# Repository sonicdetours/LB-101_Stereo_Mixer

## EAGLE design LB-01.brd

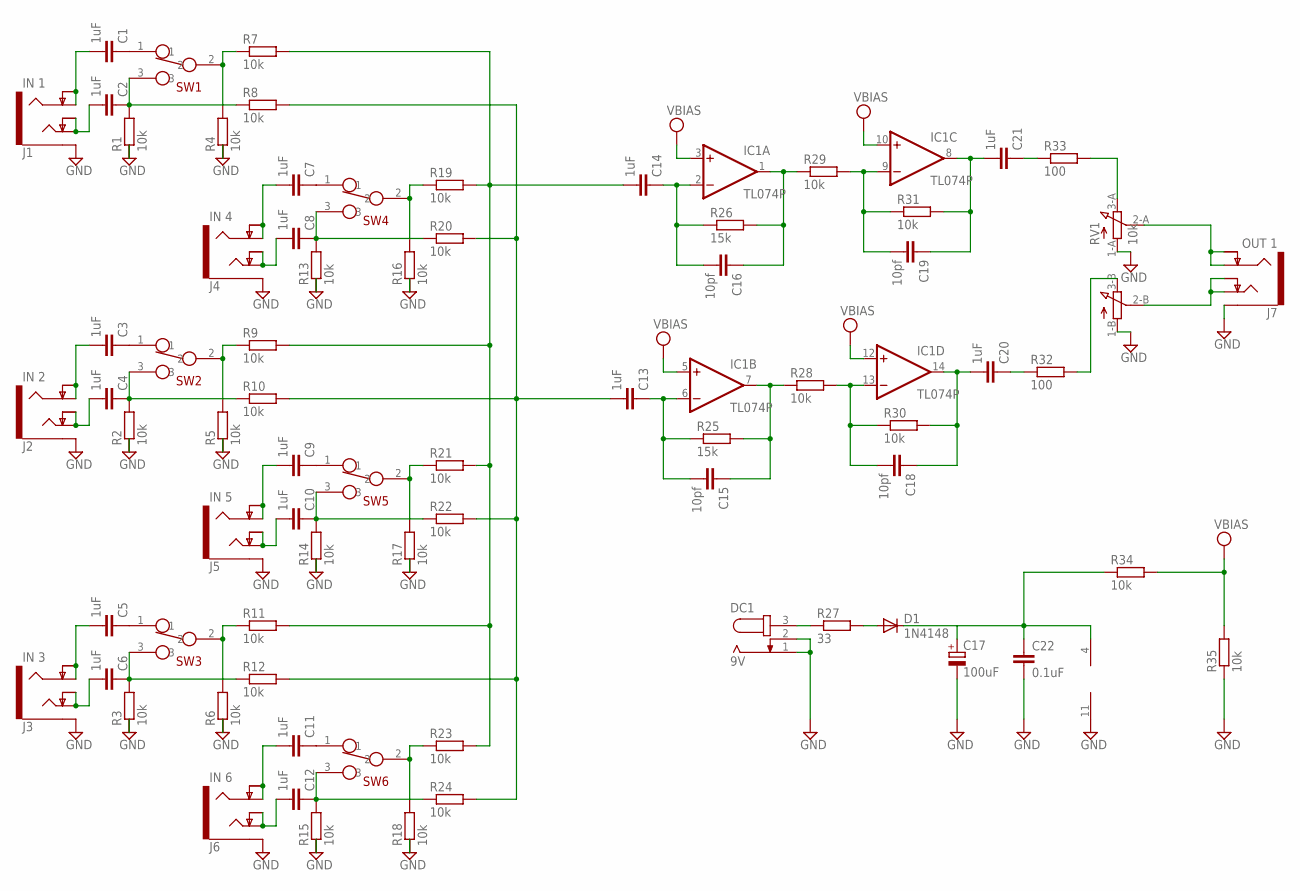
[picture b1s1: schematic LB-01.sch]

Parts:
C1, C2, C3, C4, C5, C6, C7, C8, C9, C10, C11, C12, C13, C14, C20, C21: 1uF; C-50-50
C15, C16, C18, C19: 10pf; C-25
C17: 100uF; C-POL-2.5-05
C22: 0.1uF; C-25
D1: 1N4148; DO35-10
DC1: 9V; DC-JACK
IC1: TL074P; DIL14
J1: IN 1; STEREO_JACK_3.5MM
J2: IN 2; STEREO_JACK_3.5MM
J3: IN 3; STEREO_JACK_3.5MM
J4: IN 4; STEREO_JACK_3.5MM
J5: IN 5; STEREO_JACK_3.5MM
J6: IN 6; STEREO_JACK_3.5MM
J7: OUT 1; STEREO_JACK_3.5MM
R1, R2, R3, R4, R5, R6, R7, R8, R9, R10, R11, R12, R13, R14, R15, R16, R17, R18, R19, R20, R21, R22, R23, R24, R28, R29, R30, R31, R34, R35: 10k; R-7.62MM
R25, R26: 15k; R-7.62MM
R27: 33; R-7.62MM
R32, R33: 100; R-7.62MM
RV1: 10k; POT-DUAL-PTA4544
SW1, SW2, SW3, SW4, SW5, SW6: SWITCH-SPDT; SWITCH-SPDT-SMALL

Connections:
GND: C17.-, C22.2, DC1.1, DC1.2, IC1.11 (V-), J1.SLEEVE (EARTH), J2.SLEEVE (EARTH), J3.SLEEVE (EARTH), J4.SLEEVE (EARTH), J5.SLEEVE (EARTH), J6.SLEEVE (EARTH), J7.SLEEVE (EARTH), R1.1, R2.1, R3.1, R4.1, R5.1, R6.1, R13.1, R14.1, R15.1, R16.1, R17.1, R18.1, R35.1, RV1.1-A (A-1), RV1.1-B (B-1)
unnamed: C1.2, J1.RING, J1.RING_DETECT (RING-NORM)
unnamed: C7.2, J4.RING, J4.RING_DETECT (RING-NORM)
unnamed: C2.2, J1.TIP, J1.TIP_DETECT (TIP-NORM)
unnamed: C8.2, J4.TIP, J4.TIP_DETECT (TIP-NORM)
unnamed: C2.1, R1.2, R8.1, SW1.3
unnamed: R4.2, R7.1, SW1.2
unnamed: C8.1, R13.2, R20.1, SW4.3
unnamed: C1.1, SW1.1
unnamed: R16.2, R19.1, SW4.2
unnamed: C7.1, SW4.1
unnamed: C9.2, J5.RING, J5.RING_DETECT (RING-NORM)
unnamed: C10.2, J5.TIP, J5.TIP_DETECT (TIP-NORM)
unnamed: C10.1, R14.2, R22.1, SW5.3
unnamed: R17.2, R21.1, SW5.2
unnamed: C9.1, SW5.1
unnamed: C3.2, J2.RING, J2.RING_DETECT (RING-NORM)
unnamed: C4.2, J2.TIP, J2.TIP_DETECT (TIP-NORM)
unnamed: C4.1, R2.2, R10.1, SW2.3
unnamed: R5.2, R9.1, SW2.2
unnamed: C3.1, SW2.1
unnamed: C11.2, J6.RING, J6.RING_DETECT (RING-NORM)
unnamed: C12.2, J6.TIP, J6.TIP_DETECT (TIP-NORM)
unnamed: C12.1, R15.2, R24.1, SW6.3
unnamed: R18.2, R23.1, SW6.2
unnamed: DC1.3, R27.1
unnamed: C17.+, D1.C
unnamed: D1.A, R27.2
unnamed: C11.1, SW6.1
unnamed: C5.2, J3.RING, J3.RING_DETECT (RING-NORM)
unnamed: C6.2, J3.TIP, J3.TIP_DETECT (TIP-NORM)
unnamed: C6.1, R3.2, R12.1, SW3.3
unnamed: R6.2, R11.1, SW3.2
unnamed: C5.1, SW3.1
unnamed: C14.2, R7.2, R9.2, R11.2, R19.2, R21.2, R23.2
unnamed: C13.2, R8.2, R10.2, R12.2, R20.2, R22.2, R24.2
unnamed: R33.2, RV1.3-A (A-3)
unnamed: C14.1, C16.2, IC1.2 (-IN), R26.1
unnamed: C16.1, IC1.1 (OUT), R26.2, R29.1
unnamed: C19.2, IC1.9 (-IN), R29.2, R31.1
unnamed: C19.1, C21.2, IC1.8 (OUT), R31.2
unnamed: C13.1, C15.2, IC1.6 (-IN), R25.1
unnamed: C15.1, IC1.7 (OUT), R25.2, R28.1
unnamed: C18.2, IC1.13 (-IN), R28.2, R30.1
unnamed: C18.1, C20.2, IC1.14 (OUT), R30.2
unnamed: R32.2, RV1.3-B (B-3)
unnamed: C21.1, R33.1
unnamed: C20.1, R32.1
unnamed: J7.RING, J7.RING_DETECT (RING-NORM), RV1.2-A (A-2)
unnamed: J7.TIP, J7.TIP_DETECT (TIP-NORM), RV1.2-B (B-2)
unnamed: C22.1, IC1.4 (V+), R34.1
VPP: IC1.3 (+IN), IC1.5 (+IN), IC1.10 (+IN), IC1.12 (+IN), R34.2, R35.2

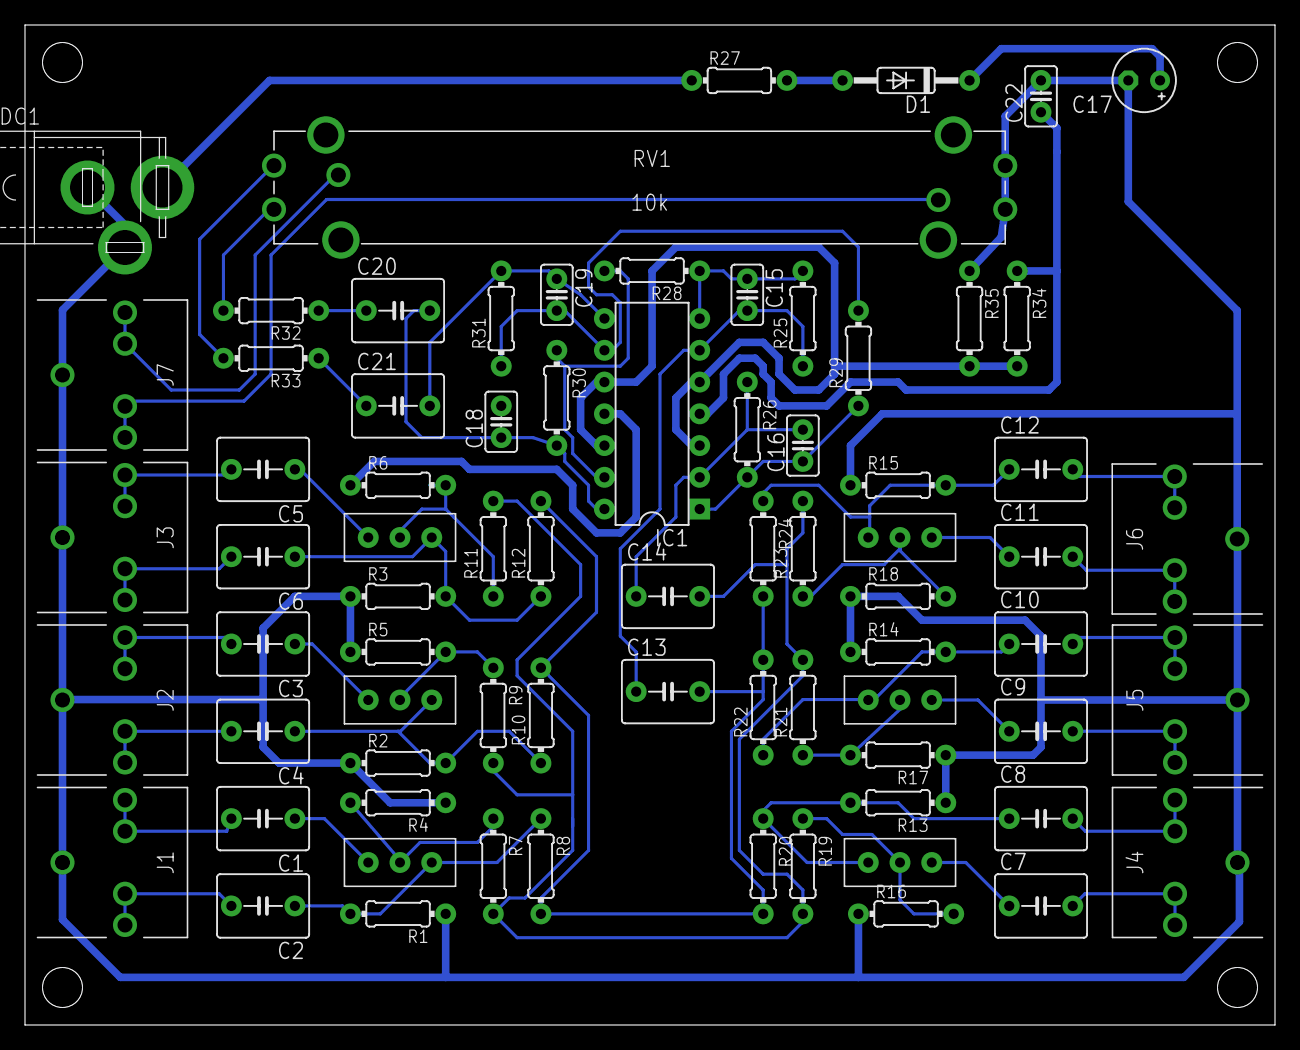
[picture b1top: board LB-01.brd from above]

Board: 2 copper layers, 100.0 x 80.0 mm, 74 parts (0 on the bottom side), 52 nets.

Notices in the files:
parts and their libraries:
sonic-detours: CC BY-SA 4.0
